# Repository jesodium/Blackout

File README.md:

wro 2026 FI [1st place in panama]

single arduino giga r1 wifi (sensors, ble) + node.js dashboard

## project layout

```
├── firmware/
│   ├── giga/main/       giga r1 wifi — sensors, motors, arm, ble (main.ino + one .h per section)
│   ├── giga/i2c_scan/   i2c bus diagnostic
│   ├── giga/motor_test/ bench motor check
│   ├── esp32-cam/main/  esp32-cam — mjpeg streamer / usb frame server
│   └── uno-r4/          bench sketches
├── server/
│   ├── server.js        entry: loads src/ and listens (electron forks this)
│   ├── mcp.mjs          mcp stdio server for claude desktop / code
│   ├── src/             server modules (link, telemetry, cam, tts, …) + sage/ (the ai agent)
│   ├── public/          dashboard: index.html, js/app.js + js/ui/ components, lib modules
│   ├── prompts/         sage's system prompts
│   ├── data/            recorded arm takes, tapes, blk workflows
│   ├── test/            npm run test:<name>
│   └── tools/           bench tools (armrec.py, …)
├── electron/            desktop shell (custom ble picker)
├── scripts/             flash.sh, arm-configurator.sh, docs.sh
├── docs/
├── archive/             retired mega 2560 + uno r3 setup (porting reference only)
└── hardware/            cad/ + step/ (local, not in git)
```

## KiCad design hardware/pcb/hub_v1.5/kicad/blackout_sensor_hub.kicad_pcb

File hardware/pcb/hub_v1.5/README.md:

# BLACKOUT Sensor Hub v1.5

**v1.6** (2026-10-19): J28 is now `GPS UART2 D19` (PH4: 3V3, GND, NEO-7M TX through R14 1k to D19, D18 to its RX), replacing the AUX A0 port. Turned 270° so its pads clear the I2C1_SCL track. Built with `source/keep.sh <outdir>` (`MP=50`, REFS default `J28 R14`). The +3V3 link to J28 pin 1 is one hand-added F.Cu track at x 161.5 (y 78.0 to 72.6), because Freerouting kept leaving it open. ERC 0, DRC 0 errors/0 unconnected, verify.py ok. The v1.5 board is in git (19eb38a).

**v1.5** (2026-10-12): J32 `W1 GYRO I2C` (PH4: 3V3, GND, SCL1, SDA1) and J33 `MQ135 5V A1` (PH4: fused 5V, GND, DO not connected, AO through R12 10k / R13 15k to A1, max 3.15 V). F1, C1, C3, C4, R10/R11 and D1/D2 moved into free gaps; C5/C6 dropped. Built with `source/keep.sh <outdir>` (`DROP="net:+5V_FUSED" MP=100`), checked with `source/verify.py`, fab files from `source/fab.py`. The v1.4 board and schematic are in `kicad/archive_v1.4/`. Ordering notes: `../README.txt`. The rest of this file describes v1.4.

This is a **Giga R1 WiFi shield that turns the rover's sensors into plug-in modules.** Every sensor gets its own keyed JST-PH port, labelled on the silkscreen with bus, address, pin names and voltage.
The three I2C buses stay separate: `Wire` feeds the arm alone. Each of Wire1 and Wire2 gets Qwiic ports for new sensors. The ports for the LIDAR, IMU and L298N are already there.
**v1.1 adds two things:**
- Every Giga header pin is named on the silkscreen, and pins the shield already uses are printed inverted.
**v1.3** adds two spare JST-PH ports for sensors added later: J28 (3-pin: 3V3, A0, GND) and J29 (4-pin: 3V3, D44, D46, GND). J31 moved 3 mm right to make room. See PINOUT.md.
**v1.4** replaces the OLED port with J11, a JST-PH8 port for a 3.5" ILI9488 SPI display ("3.5in TFT SPI 480x320 V1.0").
  - Its pin order matches pins 1-8 of the display's header, so the cable crimps straight through.
  - It uses `SPI1` (D13 SCK, D11 MOSI), with D10 for CS and D1 for DC. It also carries fused 5V.
  - The port is turned 180° so CK, DI and CS sit in the same order as D13, D11 and D10.
  - The BME280 port (J12) moved to the bottom-left corner to make room, and C4-C6 moved up 4.3 mm. All other copper is kept from v1.3.
  - J30 is labelled "EXTRA PINS".

- A spare-GPIO breakout: a 2x7 header with PWM D10-D13, Serial2 D18/D19, A1-A4, A6 and A7, next to 3V3 and GND, plus a 3V3/GND rail by the D22-D53 block.

The board is 2 layers, 101.6 × 53.34 mm (the Mega/Giga outline). Parts are on the top side only, all SMD, 0805 or larger, except the Giga headers and the L298N header.

## Status

| Check | Result |
|---|---|
| ERC (KiCad 10.0.6, all severities) | **0 errors, 0 warnings** (`reports/erc.rpt`) — v1.1 |
| DRC (all severities, schematic parity on) | **0 violations, 0 unconnected, 0 parity issues** (`reports/drc.rpt`) |
| Routing | Freerouting 2.4.1, 100 % routed. It routes at 0.22 mm clearance as a safety margin, and the board is checked at 0.2 mm. GND pour on both layers with stitching vias |

One project rule relaxes a default (`kicad/blackout_sensor_hub.kicad_dru`): a GND thermal needs only 1 spoke, not 2.
That is safe because every GND pad is also routed to GND by a track. The pour is extra.

## Why it's built this way

- **Shield, not a separate hub board.** Every pin the robot uses is already on the Mega-layout headers except D72. That covers D2-D7, D8/D9, D20/D21, the D22-D53 block, SDA1/SCL1 by AREF, A5 and the power header.
  A shield has no ribbon or harness to the Giga that could come loose, and nothing to mis-wire. The outline, the six Ø3.2 holes and the header positions come from KiCad's official Arduino_Mega template.
  I checked them against the Giga datasheet (ABX00063 §15: 101.6 × 53.34 mm, the same six holes).
- **SMD JST-PH ports everywhere, not through-hole.** Parts on the Giga poke up into the space under the shield: USB-A, the audio jack, the two camera/display headers (J5/J6), SPI and JTAG.
  An SMD port puts nothing through the board, so ports can sit anywhere. Their outlines are on the `User.Comments` layer, taken from the datasheet's top view.
  PH is keyed, and every port's pin order matches the module's own header, so each cable is crimped straight through. (A reversed VCC/GND cost the team a day on the GY-302.)
- **I2C isolation is enforced by copper.** D20/D21 go to J10 (the PCA9685) and nowhere else. A browned-out servo driver can only clamp its own bus.
  - Wire1 (SDA1/SCL1): BME280, 2× Qwiic. The OLED left in v1.4, replaced by the SPI LCD.
  - Wire2 (D9/D8): GY-302 with **ADDR hard-tied to GND** so it stays 0x23, plus 3× Qwiic for the ENS160/AHT21 and the INA219 (at 0x41).
  - The pull-ups are fitted but switched off by an open jumper, because the modules already carry their own.
- **3V3 everywhere, 5V only where it has to be.** 5V reaches only the LIDAR, the LCD (v1.4) and (by default) the relay modules' VCC.
  It comes straight from the Giga's 5V pin through a 1.1 A PTC. There is no external 5V input or MQ-2 port any more (removed in v1.2).
  The Giga's 5V pin current rating isn't published. The whole budget is LIDAR (~300 mA at start), LCD (~100 mA) and relay coils, roughly 0.8 A. That is under F1's 1.1 A hold, but more than a USB port gives, so run the rover from VIN. Nothing above 3.3 V ever reaches a Giga pin:
  - The UART inputs have 1 kΩ in series, which limits the current if a 5V-TX device is ever plugged in.
  - The LCD port is write-only. The display's SDO and touch pins aren't on it, so nothing on that cable drives a Giga pin.
    The ILI9488's logic runs at 3.3 V; only VCC is 5 V, and it feeds the module's own regulator.
- **Pinout follows the firmware, not the other way round.** The existing sensors land on exactly the pins in `main.ino` and `arm.h`: TRIG 52, ECHO 50, DHT A5, relays 26/28/30, OE 32, L298N 2-7, the three Wire objects. **No firmware change is needed.**
  The new ports follow `parts/WIRING.md`: LD19 on Serial3 (D17), BNO086 RVC on Serial4 (D15). The LD19's PWM pin is grounded by default, as its manual requires.
- **L298N header sits directly under D2-D7.** It's mirrored (pin 1 on the right) so each signal runs straight down. It keeps the L298N's own order, so the ribbon still runs straight across.

- **v1.1 pin names go on the outside of each header row.** The strip on the inside is hidden under the stacking-header housing.
  - Text is 0.8 mm tall with a 0.15 mm stroke, narrowed so a 5-letter name like `CANRX` fits the 2.54 mm pitch.
  - On the 2x18, odd numbers are printed vertically, because the board edge is only 1.7 mm from those pads.
- **v1.1 breakout: one compact 2x7 rather than servo-style rows.** Three rows of 12 would take about 34 × 12 mm, and there is no such space without dropping a port.
  - The 2x7 fits the corner where the logo used to sit. The logo moved to the edge strip and the back.
  - The top row is 3V3 + PWM/UART and the bottom row is GND + analog, so each group has a rail at its end.
  - The D22-D53 block, A8-A11, the DACs and CAN are reachable at the labelled stacking-header sockets, per the priority order. They get their own 3V3/GND rail (J31) next to JSIDE.

Not included, on purpose: a TVS/ESD array. The UART inputs are covered by the series resistors, and every other port runs to a module on the same chassis ground. Adding it would have cost board space the ports needed.
A Fritzing file was also skipped: its 2020 build can't import KiCad, and the KiCad files are the source of truth.

## Files

```
kicad/     blackout_sensor_hub.kicad_pro/.kicad_sch/.kicad_pcb/.kicad_dru, fp-lib-table,
           Blackout.pretty/ (Giga headers without silk, M3 hole without courtyard)
           archive_v1.3/ (the v1.3 board + schematic, with the OLED port)
fab/       blackout_sensor_hub_jlcpcb_v1.4.zip  <- upload this
           blackout_sensor_hub_jlcpcb_v1.3.zip  (OLED port instead of the LCD)
           blackout_sensor_hub_jlcpcb_v1.2.zip  (before the AUX ports)
           blackout_sensor_hub_jlcpcb_v1.zip    (previous revision, kept as-is)
           gerbers/ (the same files, unzipped, plus the drill map)
           bom.csv (all parts), bom_jlcpcb.csv + cpl_jlcpcb.csv (SMT assembly)
docs/      schematic.pdf, assembly_top.pdf (refdes on F.Fab), renders/ (top, bottom, iso PNG; layer SVGs)
reports/   erc.rpt, drc.rpt
source/    the generator (design.py is the single netlist+placement source) -- see "Regenerating"
PINOUT.md  every port, pin by pin, with the firmware names
```

## Ordering (JLCPCB)

1. Go to jlcpcb.com, then **Order now**, and upload `fab/blackout_sensor_hub_jlcpcb_v1.4.zip`. It should detect 2 layers, 101.6 × 53.34 mm.
2. Set: FR-4, 1.6 mm, **HASL lead-free**. **Black** solder mask with white silk suits the name (any colour works). "Remove order number": specify a location, or pay the small fee.
3. **Board only (hand-solder):** order 5 pcs, then buy the parts in `fab/bom.csv` from LCSC (every line has a C-number except the headers).
   **SMT assembly:** turn on PCB Assembly (Economic, top side). Upload `fab/bom_jlcpcb.csv` and `fab/cpl_jlcpcb.csv`.
   In the placement preview, **check the rotation of each JST connector** (JLC's footprint origins differ from KiCad's, so fix any that look wrong). The Giga headers and J22 are not in the assembly files. Solder those yourself.
4. Rough cost:
   - Five bare boards are about **US$5-10**. The board is just over 100 mm, so it misses the US$2 promo size.
   - Shipping to a Miami PO-box forwarder is about **US$15-25**.
   - Assembly for 2 boards adds roughly **US$40-60**. Most of that is a US$3 extended-part fee per unique connector/FET/PTC. The parts themselves are about US$4 per board.
   - Hand-solder parts from LCSC for 5 boards come to about **US$15-20**, plus headers.
  - v1.1 does not change the price. The board size, layer count and SMT parts are the same. It only adds a 2x7 and a 2x2 male header, about US$0.30 per board, hand-soldered.

## Assembly notes

- **Solder the SMD parts first, headers last.**
  - For the Giga headers, use an Arduino **Mega stacking-header set**, or plain male headers inserted from the bottom (J1-J7). Solder one pin per header, seat the board on the Giga, then finish, so the headers come out straight.
  - J22 (L298N) is a 1x7 male header on top. **Trim its pins flush underneath**, because it sits over the Giga.
  - J30 (the 2x7 breakout) and J31 (the 2x2 rail) are male headers on top. Trim them flush as well.
  - **Use stacking headers**, not plain male pins. That is what makes the labelled sockets usable for D22-D53, A8-A11, the DACs and CAN.
- **Buzzer:** D72 lives on the Giga's J5 display/camera header, not on any Mega header. Run a short wire from the Giga's D72 to the **TP1 `D72`** pad. JP5 ships bridged to TP1.
  To avoid the wire, cut JP5's 1-2 trace, bridge 2-3 (D34), and change `BUZZ_PIN` to 34.
- Cut or bridge the jumpers as listed in PINOUT.md. The default state matches today's firmware and the LD19 manual.
- Power-up check:
  - With the Giga on USB, **D1 green** (3V3) should light. **D2 red** (fused 5V) should light too.
  - Then run `giga-r1/i2c_scan/`. Expect 0x40 on Wire only, 0x76 on Wire1 (plus the known 0x60 ghost), and 0x23 on Wire2. The LCD isn't on I2C.
- top.png/iso.png come from a render-only copy made by `source/dress.py <board> <copy>`. It shows the Giga headers as stacking sockets and uses the through-hole PH housing to stand in for the SMD one (KiCad has no SM4-TB model). bottom.png comes from the real board. The copper is unchanged.

## Verify before ordering

1. **Print `docs/renders/top_layers.svg` at 100 % and lay the Giga on it.** Check each header row and the 2x18 JSIDE block.
   The positions come from KiCad's Mega template. The JSIDE column order was checked only against the datasheet drawing: even D-numbers on the inner column, 5V at the top, GND at the bottom. Nobody has measured it on a real board yet.
2. **Clearance above the Giga.** J5/J6 (camera/display), SPI and JTAG were placed by scaling the datasheet's top-view drawing, so they are approximate. Only the pins of J22, J30 and J31, plus the header joints, pass through the board.
   Check that J22's trimmed pins clear whatever sits under x≈43-58 mm, y≈45 mm from the board's top-left corner.
3. **Under the v1.1 breakout (0-18 mm in from the left edge, 6-13 mm down from the top edge)** the Giga has its USB-C receptacle (~3.2 mm tall) and the Wi-Fi module.
   There should be about 5 mm of clearance under trimmed pins, but check it with the board in hand. If the U.FL antenna lead is fitted, make sure it isn't pinched.
4. **The Giga's 3V3 budget.** All the 3V3 modules together (BME, BH1750, DHT, sonar, PCA logic, BNO086, ENS160, INA219) draw well under 150 mA. Arduino doesn't publish the 3V3 pin's limit, so keep that in mind before adding a power-hungry 3V3 module.
5. **Relay modules.** J21 gives the module 5V VCC and 3.3 V active-low inputs, which is the same arrangement as today. If your relay board needs its inputs at VCC level to release fully, put it on 3V3 with JP4, or use a 3.3V-logic board.
6. **LCSC part numbers were checked on lcsc.com** (each C-number resolves to that exact part), but not for stock or basic/extended status on the day you order.
7. The files are **KiCad 10** format and won't open in KiCad 9 or older.

## Regenerating

**Adding a part without re-routing everything (how v1.3 was made):** a full `build.sh` re-route no longer comes out clean (Freerouting leaves ~16 gaps), so v1.3 kept the v1.2 copper:
`gen_sch.py` + `mklib.py` + `gen_pcb.py` into an out dir, then `keep_route.py <old routed board> <new placed board> J28 J29 J31`, then DSN export + Freerouting + `fin.py` as in `route.sh`/`build.sh`. Only the copper around the new/moved parts changes.
v1.4 was made the same way from `kicad/archive_v1.3/` with `keep_route.py ... J11 J12 C4 C5 C6 J4` and Freerouting `-mp 100`. Runs at 150, 300 and 400 left gaps, so if it doesn't come out clean, try a few `MP` values.

`source/` rebuilds everything from `design.py`, which holds the netlist and the placement:
`build.sh` → schematic → footprint library → placed board → Freerouting → GND stitching and pour → ERC/DRC.

It needs:
- KiCad 10 at `~/Applications/KiCad/KiCad.app`, for its bundled python (`pcbnew`) and `kicad-cli`.
- An OpenJDK.
- `freerouting.jar` (v2.4.1) next to the scripts.
- KiCad's `Arduino_Mega` template, stripped down to `tmpl/base.kicad_pcb`.

Freerouting's result shifts with small placement changes, so re-check DRC after any edit.

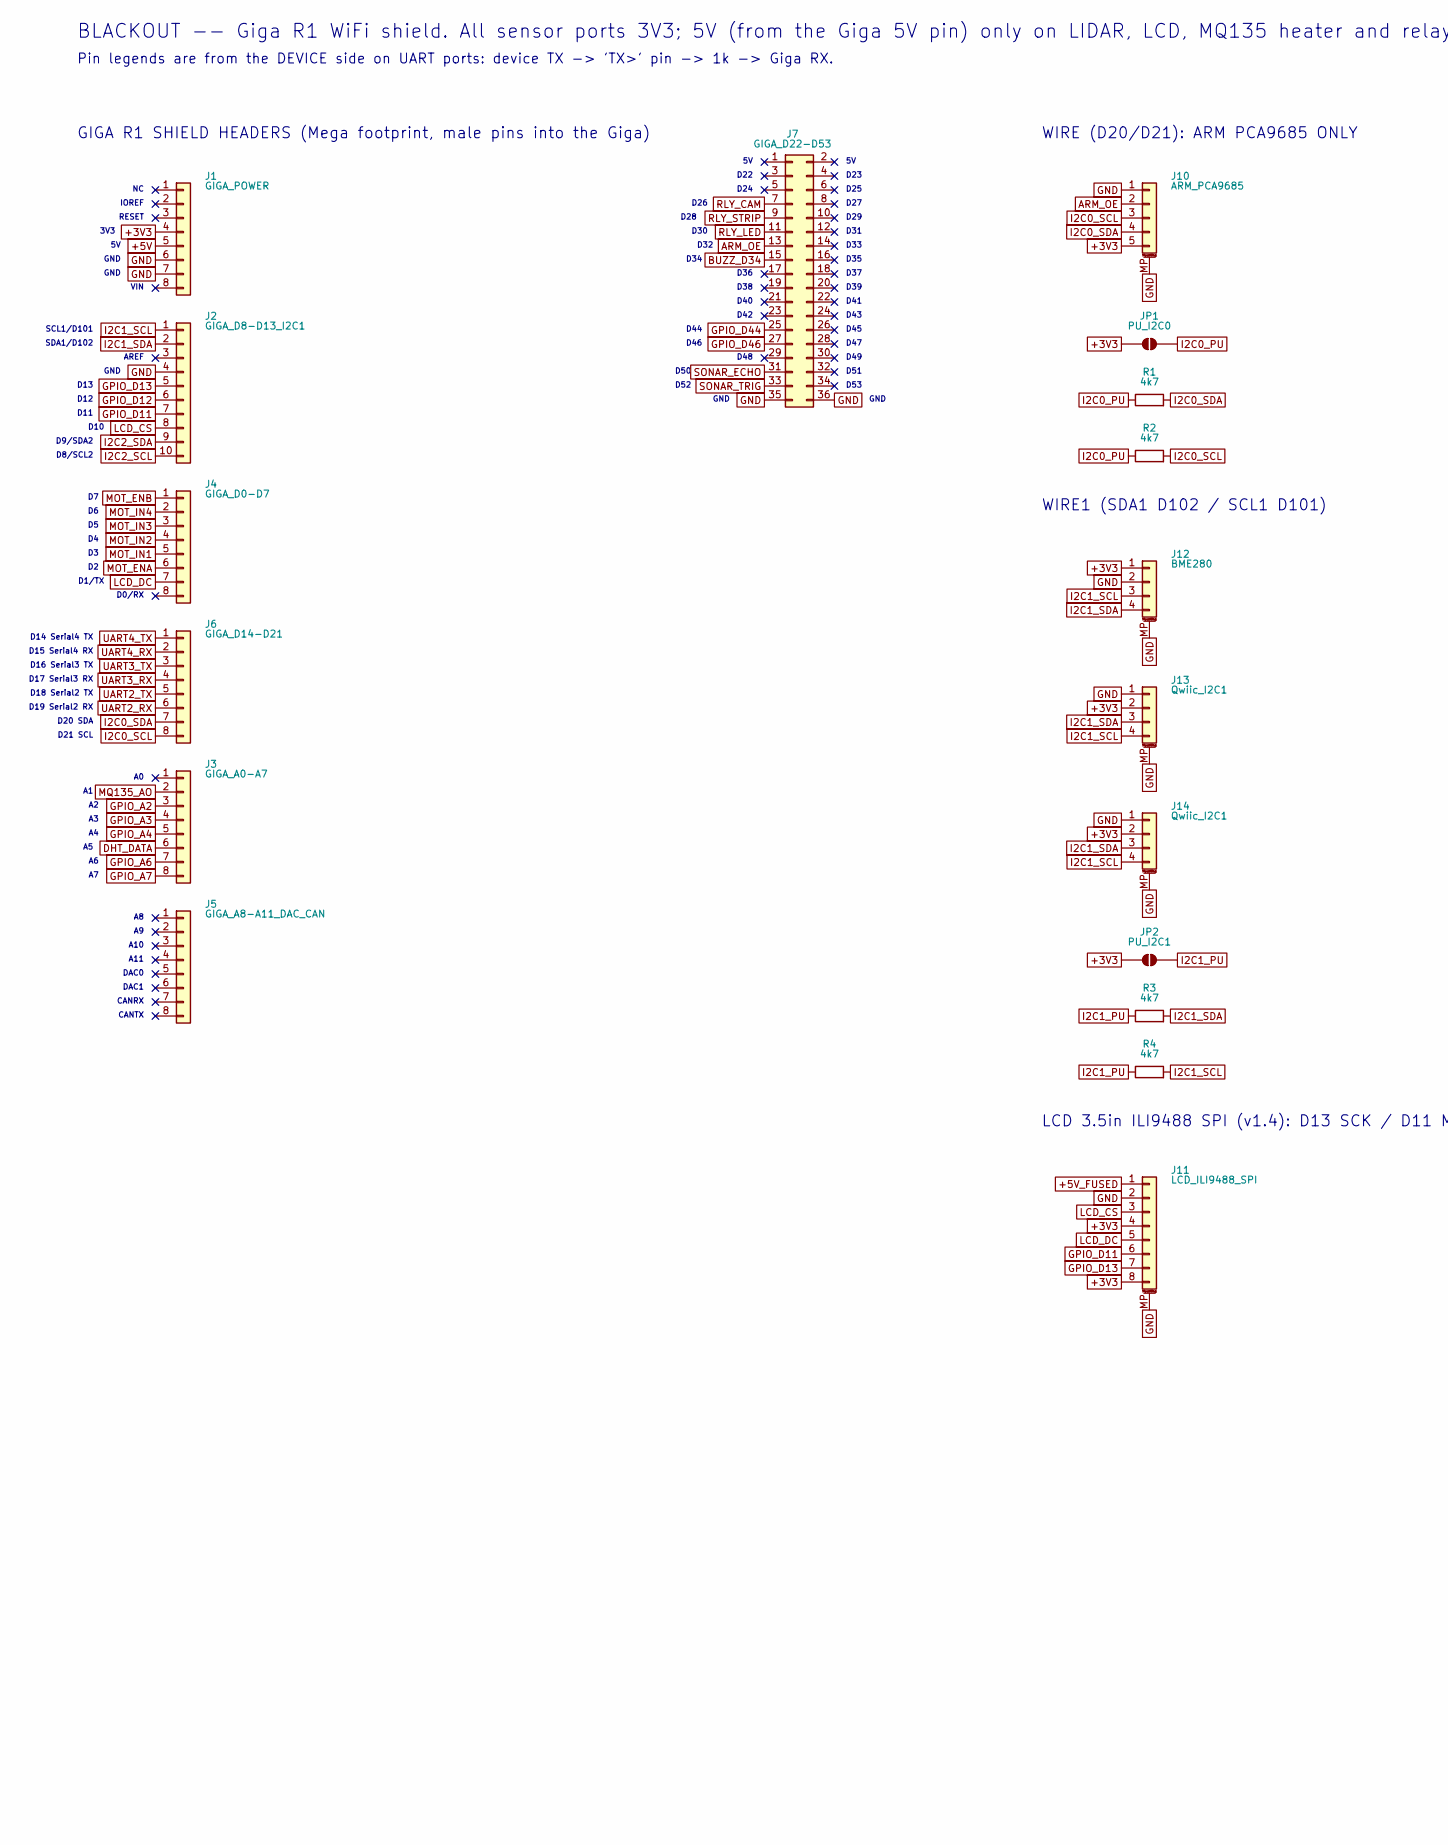
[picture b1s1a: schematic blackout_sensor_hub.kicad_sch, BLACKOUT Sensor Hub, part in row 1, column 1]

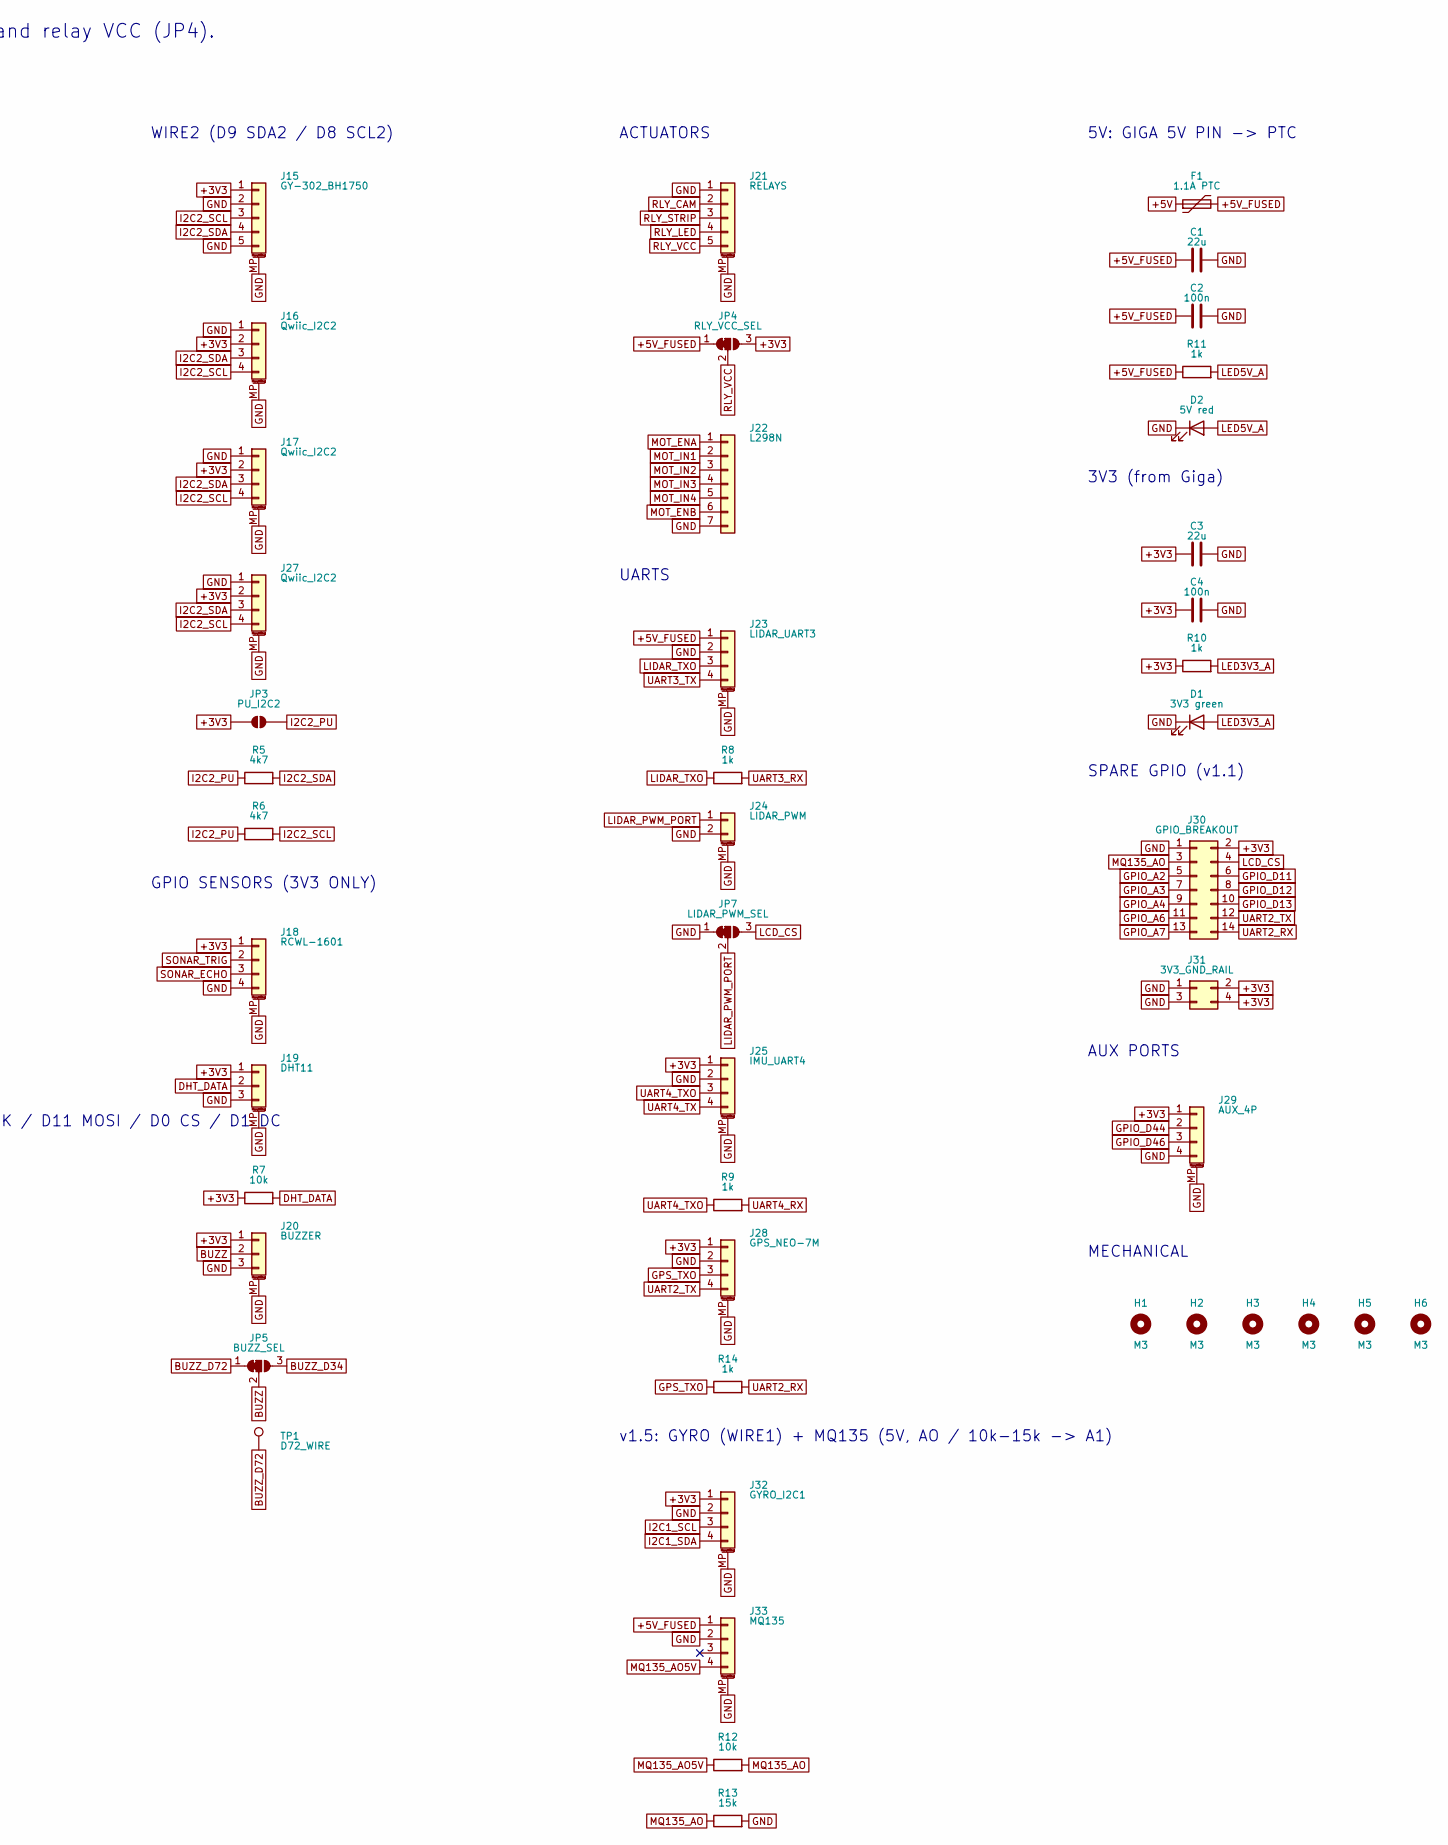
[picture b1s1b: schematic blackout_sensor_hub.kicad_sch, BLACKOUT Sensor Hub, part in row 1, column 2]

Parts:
C1, C3: 22u; C_1206_3216Metric_Pad1.33x1.80mm_HandSolder; MPN Samsung CL31A226KAHNNNE 25V 1206; LCSC C12891
C2, C4: 100n; C_0805_2012Metric_Pad1.18x1.45mm_HandSolder; MPN YAGEO CC0805KRX7R9BB104; LCSC C49678
D1: 3V3 green; LED_0805_2012Metric_Pad1.15x1.40mm_HandSolder; MPN KENTO KT-0805G; LCSC C2297
D2: 5V red; LED_0805_2012Metric_Pad1.15x1.40mm_HandSolder; MPN NATIONSTAR NCD0805R1; LCSC C84256
F1: 1.1A PTC; Fuse_1206_3216Metric_Pad1.42x1.75mm_HandSolder; MPN PTTC SMD1206P110TF/16 1.1A hold; LCSC C523825
H1, H2, H3, H4, H5, H6: M3; MountingHole_3.2mm_M3_Shield
J1: GIGA_POWER; Giga_Header_1x08_P2.54mm
J2: GIGA_D8-D13_I2C1; Giga_Header_1x10_P2.54mm
J3: GIGA_A0-A7; Giga_Header_1x08_P2.54mm
J4: GIGA_D0-D7; Giga_Header_1x08_P2.54mm
J5: GIGA_A8-A11_DAC_CAN; Giga_Header_1x08_P2.54mm
J6: GIGA_D14-D21; Giga_Header_1x08_P2.54mm
J7: GIGA_D22-D53; Giga_Header_2x18_P2.54mm
J10: ARM_PCA9685; JST_PH_B5B-PH-SM4-TB_1x05-1MP_P2.00mm_Vertical; MPN JST B5B-PH-SM4-TB(LF)(SN); LCSC C265085
J11: LCD_ILI9488_SPI; JST_PH_B8B-PH-SM4-TB_1x08-1MP_P2.00mm_Vertical; MPN JST B8B-PH-SM4-TB(LF)(SN); LCSC C495548
J12: BME280; JST_PH_B4B-PH-SM4-TB_1x04-1MP_P2.00mm_Vertical; MPN JST B4B-PH-SM4-TB(LF)(SN); LCSC C160354
J13, J14: Qwiic_I2C1; JST_SH_BM04B-SRSS-TB_1x04-1MP_P1.00mm_Vertical; MPN JST BM04B-SRSS-TB(LF)(SN); LCSC C160390
J15: GY-302_BH1750; JST_PH_B5B-PH-SM4-TB_1x05-1MP_P2.00mm_Vertical; MPN JST B5B-PH-SM4-TB(LF)(SN); LCSC C265085
J16, J17, J27: Qwiic_I2C2; JST_SH_BM04B-SRSS-TB_1x04-1MP_P1.00mm_Vertical; MPN JST BM04B-SRSS-TB(LF)(SN); LCSC C160390
J18: RCWL-1601; JST_PH_B4B-PH-SM4-TB_1x04-1MP_P2.00mm_Vertical; MPN JST B4B-PH-SM4-TB(LF)(SN); LCSC C160354
J19: DHT11; JST_PH_B3B-PH-SM4-TB_1x03-1MP_P2.00mm_Vertical; MPN JST B3B-PH-SM4-TB(LF)(SN); LCSC C160353
J20: BUZZER; JST_PH_B3B-PH-SM4-TB_1x03-1MP_P2.00mm_Vertical; MPN JST B3B-PH-SM4-TB(LF)(SN); LCSC C160353
J21: RELAYS; JST_PH_B5B-PH-SM4-TB_1x05-1MP_P2.00mm_Vertical; MPN JST B5B-PH-SM4-TB(LF)(SN); LCSC C265085
J22: L298N; PinHeader_1x07_P2.54mm_Vertical
J23: LIDAR_UART3; JST_PH_B4B-PH-SM4-TB_1x04-1MP_P2.00mm_Vertical; MPN JST B4B-PH-SM4-TB(LF)(SN); LCSC C160354
J24: LIDAR_PWM; JST_PH_B2B-PH-SM4-TB_1x02-1MP_P2.00mm_Vertical; MPN JST B2B-PH-SM4-TB(LF)(SN); LCSC C160352
J25: IMU_UART4; JST_PH_B4B-PH-SM4-TB_1x04-1MP_P2.00mm_Vertical; MPN JST B4B-PH-SM4-TB(LF)(SN); LCSC C160354
J28: GPS_NEO-7M; JST_PH_B4B-PH-SM4-TB_1x04-1MP_P2.00mm_Vertical; MPN JST B4B-PH-SM4-TB(LF)(SN); LCSC C160354
J29: AUX_4P; JST_PH_B4B-PH-SM4-TB_1x04-1MP_P2.00mm_Vertical; MPN JST B4B-PH-SM4-TB(LF)(SN); LCSC C160354
J30: GPIO_BREAKOUT; Breakout_2x07_P2.54mm
J31: 3V3_GND_RAIL; Breakout_2x02_P2.54mm
J32: GYRO_I2C1; JST_PH_B4B-PH-SM4-TB_1x04-1MP_P2.00mm_Vertical; MPN JST B4B-PH-SM4-TB(LF)(SN); LCSC C160354
J33: MQ135; JST_PH_B4B-PH-SM4-TB_1x04-1MP_P2.00mm_Vertical; MPN JST B4B-PH-SM4-TB(LF)(SN); LCSC C160354
JP1: PU_I2C0; SolderJumper-2_P1.3mm_Open_RoundedPad1.0x1.5mm
JP2: PU_I2C1; SolderJumper-2_P1.3mm_Open_RoundedPad1.0x1.5mm
JP3: PU_I2C2; SolderJumper-2_P1.3mm_Open_RoundedPad1.0x1.5mm
JP4: RLY_VCC_SEL; SolderJumper-3_P1.3mm_Bridged12_RoundedPad1.0x1.5mm
JP5: BUZZ_SEL; SolderJumper-3_P1.3mm_Bridged12_RoundedPad1.0x1.5mm
JP7: LIDAR_PWM_SEL; SolderJumper-3_P1.3mm_Bridged12_RoundedPad1.0x1.5mm
R1, R2, R3, R4, R5, R6: 4k7; R_0805_2012Metric_Pad1.20x1.40mm_HandSolder; MPN UNI-ROYAL 0805W8F4701T5E; LCSC C17673
R7, R12: 10k; R_0805_2012Metric_Pad1.20x1.40mm_HandSolder; MPN UNI-ROYAL 0805W8F1002T5E; LCSC C17414
R8, R9, R10, R11, R14: 1k; R_0805_2012Metric_Pad1.20x1.40mm_HandSolder; MPN UNI-ROYAL 0805W8F1001T5E; LCSC C17513
R13: 15k; R_0805_2012Metric_Pad1.20x1.40mm_HandSolder; MPN UNI-ROYAL 0805W8F1502T5E; LCSC C17475
TP1: D72_WIRE; TestPoint_Pad_2.0x2.0mm

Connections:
+3V3: C3.1, C4.1, J1.4, J10.5, J11.4, J11.8, J12.1, J13.2, J14.2, J15.1, J16.2, J17.2, J18.1, J19.1, J20.1, J25.1, J27.2, J28.1, J29.1, J30.2, J31.2, J31.4, J32.1, JP1.1 (A), JP2.1 (A), JP3.1 (A), JP4.3 (B), R7.1, R10.1
+5V: F1.1, J1.5
+5V_FUSED: C1.1, C2.1, F1.2, J11.1, J23.1, J33.1, JP4.1 (A), R11.1
ARM_OE: J7.13, J10.2
BUZZ: J20.2, JP5.2 (C)
BUZZ_D34: J7.15, JP5.3 (B)
BUZZ_D72: JP5.1 (A), TP1.1
DHT_DATA: J3.6, J19.2, R7.2
GND: C1.2, C2.2, C3.2, C4.2, D1.1 (K), D2.1 (K), J1.6, J1.7, J2.4, J7.35, J7.36, J10.1, J10.MP (MountPin), J11.2, J11.MP (MountPin), J12.2, J12.MP (MountPin), J13.1, J13.MP (MountPin), J14.1, J14.MP (MountPin), J15.2, J15.5, J15.MP (MountPin), J16.1, J16.MP (MountPin), J17.1, J17.MP (MountPin), J18.4, J18.MP (MountPin), J19.3, J19.MP (MountPin), J20.3, J20.MP (MountPin), J21.1, J21.MP (MountPin), J22.7, J23.2, J23.MP (MountPin), J24.2, J24.MP (MountPin), J25.2, J25.MP (MountPin), J27.1, J27.MP (MountPin), J28.2, J28.MP (MountPin), J29.4, J29.MP (MountPin), J30.1, J31.1, J31.3, J32.2, J32.MP (MountPin), J33.2, J33.MP (MountPin), JP7.1 (A), R13.2
GPIO_A2: J3.3, J30.5
GPIO_A3: J3.4, J30.7
GPIO_A4: J3.5, J30.9
GPIO_A6: J3.7, J30.11
GPIO_A7: J3.8, J30.13
GPIO_D11: J2.7, J11.6, J30.6
GPIO_D12: J2.6, J30.8
GPIO_D13: J2.5, J11.7, J30.10
GPIO_D44: J7.25, J29.2
GPIO_D46: J7.27, J29.3
GPS_TXO: J28.3, R14.1
I2C0_PU: JP1.2 (B), R1.1, R2.1
I2C0_SCL: J6.8, J10.3, R2.2
I2C0_SDA: J6.7, J10.4, R1.2
I2C1_PU: JP2.2 (B), R3.1, R4.1
I2C1_SCL: J2.1, J12.3, J13.4, J14.4, J32.3, R4.2
I2C1_SDA: J2.2, J12.4, J13.3, J14.3, J32.4, R3.2
I2C2_PU: JP3.2 (B), R5.1, R6.1
I2C2_SCL: J2.10, J15.3, J16.4, J17.4, J27.4, R6.2
I2C2_SDA: J2.9, J15.4, J16.3, J17.3, J27.3, R5.2
LCD_CS: J2.8, J11.3, J30.4, JP7.3 (B)
LCD_DC: J4.7, J11.5
LED3V3_A: D1.2 (A), R10.2
LED5V_A: D2.2 (A), R11.2
LIDAR_PWM_PORT: J24.1, JP7.2 (C)
LIDAR_TXO: J23.3, R8.1
MOT_ENA: J4.6, J22.1
MOT_ENB: J4.1, J22.6
MOT_IN1: J4.5, J22.2
MOT_IN2: J4.4, J22.3
MOT_IN3: J4.3, J22.4
MOT_IN4: J4.2, J22.5
MQ135_AO: J3.2, J30.3, R12.2, R13.1
MQ135_AO5V: J33.4, R12.1
RLY_CAM: J7.7, J21.2
RLY_LED: J7.11, J21.4
RLY_STRIP: J7.9, J21.3
RLY_VCC: J21.5, JP4.2 (C)
SONAR_ECHO: J7.31, J18.3
SONAR_TRIG: J7.33, J18.2
UART2_RX: J6.6, J30.14, R14.2
UART2_TX: J6.5, J28.4, J30.12
UART3_RX: J6.4, R8.2
UART3_TX: J6.3, J23.4
UART4_RX: J6.2, R9.2
UART4_TX: J6.1, J25.4
UART4_TXO: J25.3, R9.1

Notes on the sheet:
GIGA R1 SHIELD HEADERS (Mega footprint, male pins into the Giga)
IOREF
RESET
3V3
GND
VIN
SCL1/D101
SDA1/D102
AREF
D13
D12
D11
D10
D9/SDA2
D8/SCL2
D1/TX
D0/RX
D14 Serial4 TX
D15 Serial4 RX
D16 Serial3 TX
D17 Serial3 RX
D18 Serial2 TX
D19 Serial2 RX
D20 SDA
D21 SCL
A10
A11
DAC0
DAC1
CANRX
CANTX
D22
D23
D24
D25
D26
D27
D28
D29
D30

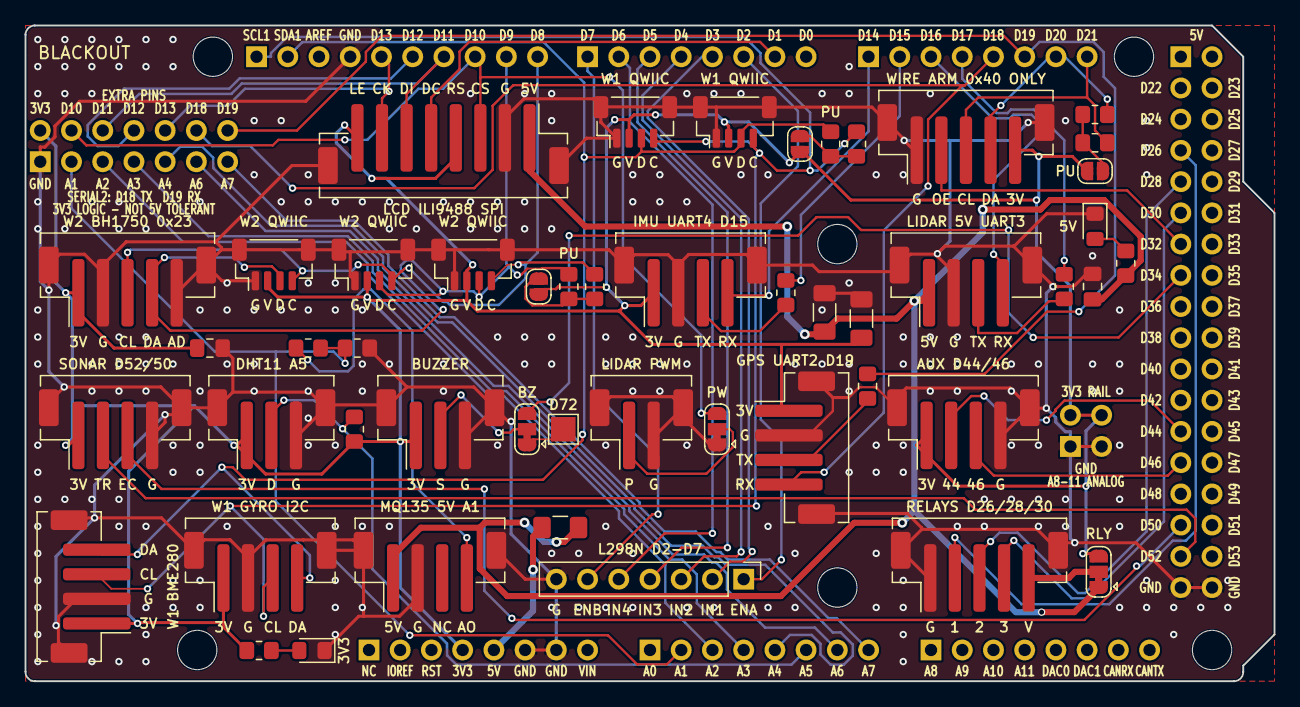
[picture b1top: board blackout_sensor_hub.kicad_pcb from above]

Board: 2 copper layers, 101.6 x 53.3 mm, 64 parts (0 on the bottom side), 56 nets.

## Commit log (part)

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2026-05-28 Add new STL file for MK2 rockers
2026-05-28 Initialize Arduino Mega project with main code, README, AGENTS, and configuration files
2026-05-30 Add telemetry dashboard with real-time sensor data visualization
    - Implemented socket connection for real-time data updates.
    - Created a typewriter effect for displaying AI analysis.
    - Developed a telemetry plotter for visualizing sensor data over time.
    - Added sparkline graphs for individual sensor readings.
    - Implemented a logging system with filters for different log types.
    - Created a 3D scene using Three.js to visualize the rover model and its telemetry data.
2026-05-30 Remove obsolete STL files for MK2 components including Brace_frame, Pivot_cap, belly_frame, climber wheel, main_frame, mid_frame, and rockers.
2026-05-30 feat: add server implementation for rover exploration AI with serial data handling and OpenAI integration
2026-06-01 feat: integrate Cerebras API for AI analysis and enhance AI command center UI
2026-06-10 refactor: consolidate server dashboard JS into app.js/scene.js, clean up dead code
2026-06-10 chore: add issue/PR templates, CI workflow, dependabot, README
2026-06-10 chore: drop issue/PR templates (solo repo)
2026-06-10 chore(deps): bump the production-deps group in /server with 4 updates
    Bumps the production-deps group in /server with 4 updates: [dotenv](https://github.com/motdotla/dotenv), [express](https://github.com/expressjs/express), [openai](https://github.com/openai/openai-nod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
    Updates `dotenv` from 16.6.1 to 17.4.2
    - [Changelog](https://github.com/motdotla/dotenv/blob/master/CHANGELOG.md)
    - [Commits](https://github.com/motdotla/dotenv/compare/v16.6.1...v17.4.2)
    Updates `express` from 4.22.2 to 5.2.1
    - [Release notes](https://github.com/expressjs/express/releases)
2026-06-10 feat: add MQ-9 sensor support for CO detection and update data handling
2026-06-17 Refactor UI components and improve styling; update font and color scheme
    - Updated font links in index.html to use Anton and Archivo for improved readability.
    - Refactored app.js to enhance UI structure, including new Head component for section headers.
    - Improved styling for trends, readings, and logs panels for better visual hierarchy.
    - Adjusted color scheme for better contrast and aesthetics in graphs and UI elements.
    - Added new Ticker component for real-time data display.
    - Introduced power management documentation in POWER.md for clearer wiring instructions.
2026-06-17 feat: remove HC-05 AT-command passthrough example code
2026-06-18 feat: integrate Microsoft Edge TTS for voice synthesis and enhance agent UI
    - Added msedge-tts package for TTS functionality via server proxy.
    - Implemented TTS endpoint to stream audio responses from Microsoft Edge neural voices.
    - Updated agent UI to reflect mood and intent based on sensor data and AI analysis.
    - Enhanced CSS for agent animations and speech display.
    - Refactored speech synthesis logic to include fallback to browser TTS.
    - Improved AI analysis prompt and response handling for better operator communication.
2026-06-18 chore(deps): bump openai
    Bumps the production-deps group with 1 update in the /server directory: [openai](https://github.com/openai/openai-node).
    Updates `openai` from 6.42.0 to 6.44.0
    - [Release notes](https://github.com/openai/openai-node/releases)
    - [Changelog](https://github.com/openai/openai-node/blob/main/CHANGELOG.md)
    - [Commits](https://github.com/openai/openai-node/compare/v6.42.0...v6.44.0)
    ---
2026-06-21 remove HC-06 code, clean firmware, prep for ESP32 serial relay
2026-06-21 switch to ESP32-CAM Bluetooth SPP relay, update power/docs
2026-06-22 refactor: remove ESP32-CAM Bluetooth code and configuration files
2026-06-23 feat: i18n, BT bridge, agent language switching, pre-rendered onboarding audio
2026-06-24 feat: update TTS provider handling, add support for Deepgram and Edge selection
2026-06-24 feat: Sage agent persona + female TTS voice, code screenshots
    Rename AI agent BLACKOUT -> Sage (female), self-introduces by name.
    DG voice -> female (Thalia en / Selena es, neutral Latin American).
    Edge fallback voices -> female. Add docs/code-shots for the writeup.
    Claude-Session: https://claude.ai/code/session_016Gb5thD9sTSjCVnCAMy4JD
2026-06-25 feat: migrate Uno to L298N, bridge data-flow check, stale sensor UI
    - arduino-uno: drop dead L293D shield (couldn't reverse), rewrite for
    L298N dual H-bridge with per-side INV flags; remove motors.cpp/.h
    - esp32: correct RX pin to GPIO19
    - server: bridge/start now waits up to 8s for ESP32 data, fails honestly
    if none arrives; add stale/unavailable sensor styling + i18n strings
    Claude-Session: https://claude.ai/code/session_01URcr372sdfbiJmsu3yuBv4
